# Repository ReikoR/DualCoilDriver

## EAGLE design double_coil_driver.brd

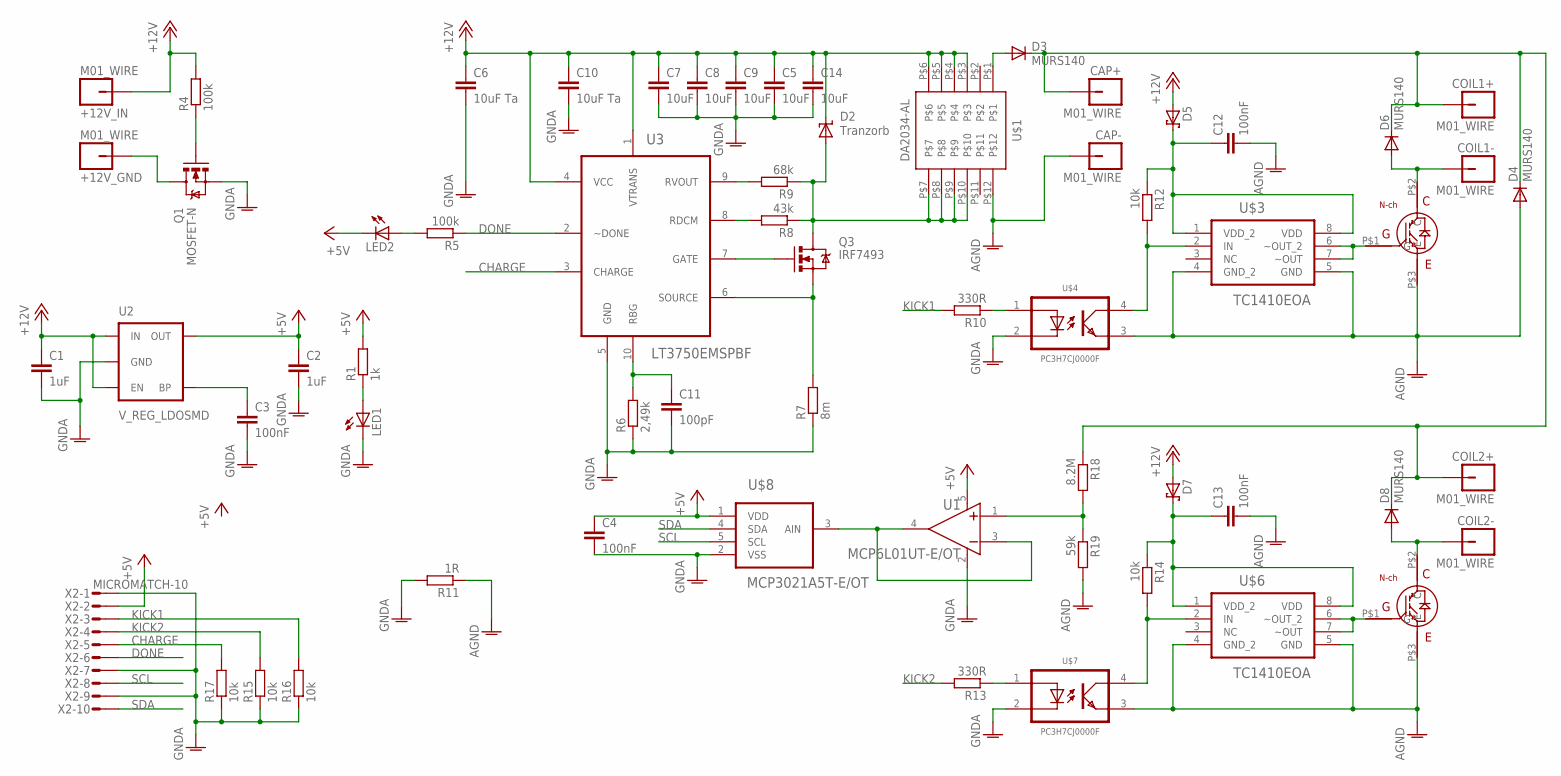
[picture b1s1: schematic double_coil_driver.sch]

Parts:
+12V_GND, +12V_IN: M01_WIRE; WIRE_HOLE
C1, C2: 1uF; C1206K
C3, C4, C12, C13: 100nF; C0603K
C5, C7, C8, C9, C14: 10uF; C1210K
C6, C10: 10uF Ta; C1210K
C11: 100pF; C0603
CAP+: M01_WIRE; WIRE_HOLE
CAP-: M01_WIRE; WIRE_HOLE
COIL1+, COIL1-, COIL2+, COIL2-: M01_WIRE; WIRE_HOLE
D2: Tranzorb; SMC
D3, D4, D6, D8: MURS140; DO214AA
D5, D7: SCHOTTKY-DIODE; SOD123
LED1, LED2: LEDCHIP-LED0603; CHIP-LED0603
Q1: MOSFET-N; SO08
Q3: IRF7493; SO08
R1: 1k; R0603
R4, R5: 100k; R0603
R6: 2,49k; R0603
R7: 8m; R2010
R8: 43k; R0603
R9: 68k; R0603
R10, R13: 330R; R0603
R11: 1R; R0603
R12, R14, R15, R16, R17: 10k; R0603
R18: 8.2M; R0603
R19: 59k; R0603
U1: MCP6L01UT-E/OT; SOT95P270X145-5N
U2: V_REG_LDOSMD; SOT23-5
U3: LT3750EMSPBF; SOP50P490X110-10N
U$1: DA2034-AL
U$2, U$5: TO-247A; TO-247
U$3, U$6: TC1410EOA; SOIC127P600X175-8N
U$4, U$7: PC3H7CJ0000F; MINI-FLAT-HALF-PITCH-4
U$8: MCP3021A5T-E/OT; SOT95P270X145-5N
X2: MICROMATCH-10

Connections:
+5V: C2.1, C4.1, LED2.C, R1.2, U1.5 (VDD), U2.5 (OUT), U$8.1 (VDD), X2.2
+12V: +12V_IN.P$1, C1.1, C5.1, C6.1, C7.1, C8.1, C9.1, C10.1, C14.1, D2.C, D5.A, D7.A, R4.2, U2.1 (IN), U2.3 (EN), U3.1 (VTRANS), U3.4 (VCC), U$1.P$3, U$1.P$4, U$1.P$5, U$1.P$6
AGND: C12.2, C13.2, CAP-.P$1, D4.A, R11.1, R19.2, U$1.P$12, U$2.P$3 (E), U$3.4 (GND_2), U$3.5 (GND), U$4.3, U$5.P$3 (E), U$6.4 (GND_2), U$6.5 (GND), U$7.3
CHARGE: R17.2, U3.3 (CHARGE), X2.5
DONE: R5.1, U3.2 (~DONE), X2.6
GNDA: C1.2, C2.2, C3.2, C4.2, C5.2, C6.2, C7.2, C8.2, C9.2, C10.2, C11.2, C14.2, LED1.C, Q1.1 (S), Q1.2 (S), Q1.3 (S), R6.1, R7.1, R11.2, R15.1, R16.1, R17.1, U1.2 (VSS), U2.2 (GND), U3.5 (GND), U$4.2, U$7.2, U$8.2 (VSS), X2.1, X2.7, X2.9
KICK1: R10.2, R16.2, X2.3
KICK2: R13.2, R15.2, X2.4
unnamed: +12V_GND.P$1, Q1.5 (D), Q1.6 (D), Q1.7 (D), Q1.8 (D)
unnamed: C3.1, U2.4 (BP)
unnamed: R18.2, R19.1, U1.1 (VIN+)
unnamed: LED1.A, R1.1
unnamed: U1.3 (VIN-), U1.4 (VOUT), U$8.3 (AIN)
unnamed: Q3.4 (G), U3.7 (GATE)
unnamed: Q1.4 (G), R4.1
unnamed: LED2.A, R5.2
unnamed: C11.1, R6.2, U3.10 (RBG)
unnamed: Q3.1 (S), Q3.2 (S), Q3.3 (S), R7.2, U3.6 (SOURCE)
unnamed: R8.2, U3.8 (RDCM)
unnamed: R9.2, U3.9 (RVOUT)
unnamed: D2.A, Q3.5 (D), Q3.6 (D), Q3.7 (D), Q3.8 (D), R8.1, R9.1, U$1.P$7, U$1.P$8, U$1.P$9, U$1.P$10
unnamed: D3.A, U$1.P$1
unnamed: CAP+.P$1, COIL1+.P$1, COIL2+.P$1, D3.C, D4.C, D6.C, D8.C, R18.1
unnamed: COIL1-.P$1, D6.A, U$2.P$2 (C)
unnamed: U$2.P$1 (G), U$3.6 (~OUT_2), U$3.7 (~OUT)
unnamed: R12.2, U$3.2 (IN), U$4.4
unnamed: R10.1, U$4.1
unnamed: C12.1, D5.C, R12.1, U$3.1 (VDD_2), U$3.8 (VDD)
unnamed: COIL2-.P$1, D8.A, U$5.P$2 (C)
unnamed: U$5.P$1 (G), U$6.6 (~OUT_2), U$6.7 (~OUT)
unnamed: R14.2, U$6.2 (IN), U$7.4
unnamed: R13.1, U$7.1
unnamed: C13.1, D7.C, R14.1, U$6.1 (VDD_2), U$6.8 (VDD)
SCL: U$8.5 (SCL), X2.8
SDA: U$8.4 (SDA), X2.10

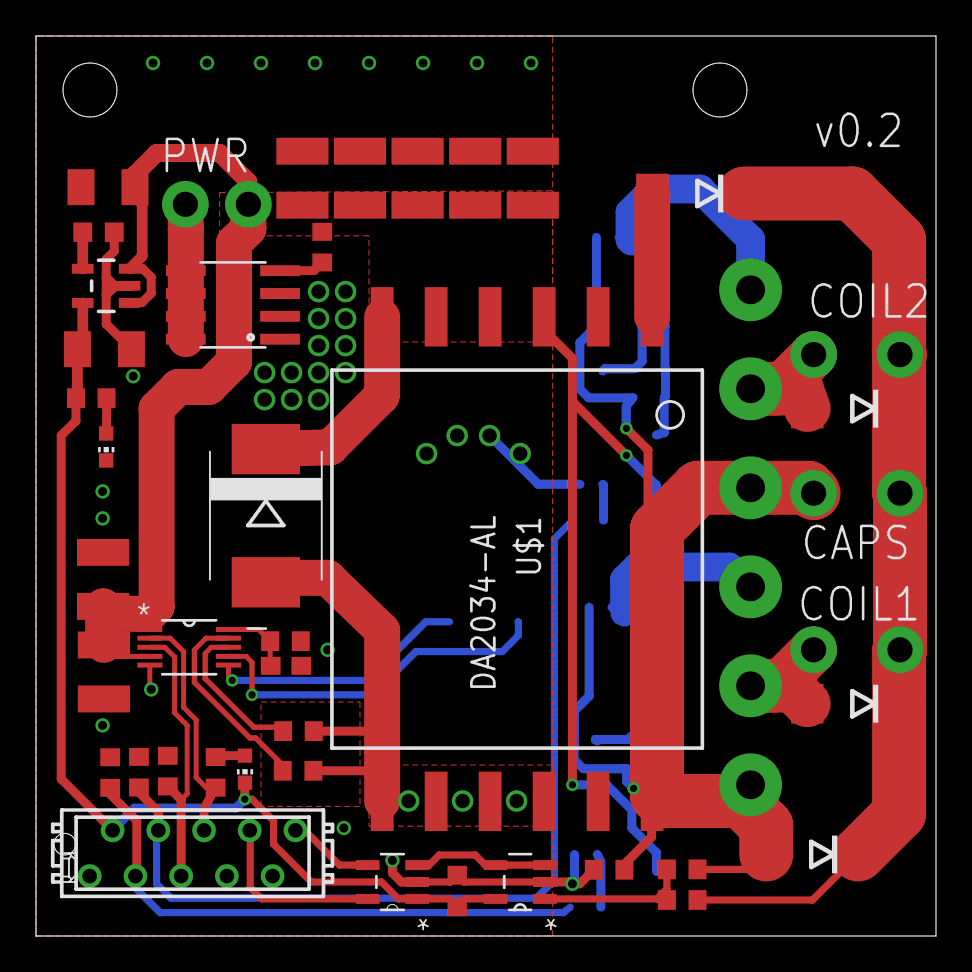
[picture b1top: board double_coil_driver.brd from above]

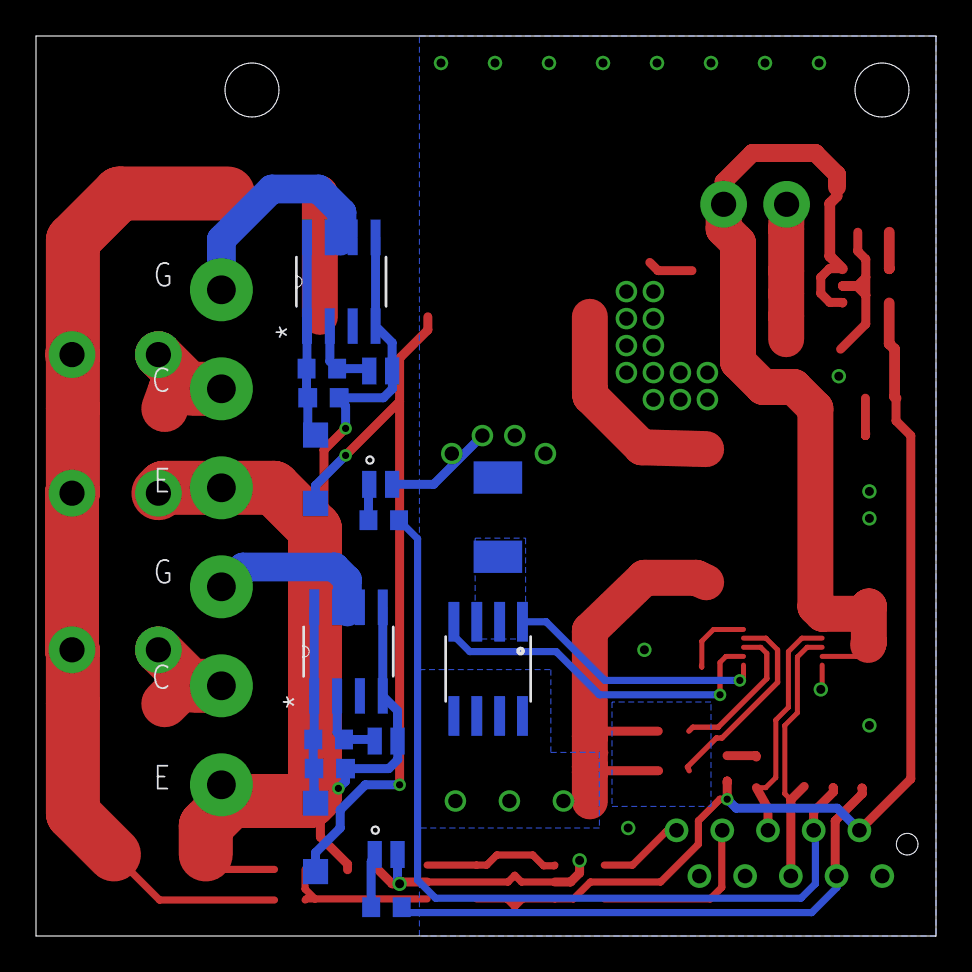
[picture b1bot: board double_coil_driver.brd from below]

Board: 2 copper layers, 50.0 x 50.0 mm, 62 parts (16 on the bottom side), 35 nets.

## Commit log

2013-12-23 Schematic with half finished board layout
2013-12-29 Added opamp to ADC, changed board layout a bit
2014-03-23 Changed board layout
2014-05-10 Added MicroMatch hole and some labels
2014-07-20 Added missing capacitor values
2014-10-27 Changed kick pull-ups to pull-downs

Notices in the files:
parts and their libraries:
SparkFun-PowerIC: Licensing: CC v3.0 Share-Alike You are welcome to use this library for commercial purposes.
